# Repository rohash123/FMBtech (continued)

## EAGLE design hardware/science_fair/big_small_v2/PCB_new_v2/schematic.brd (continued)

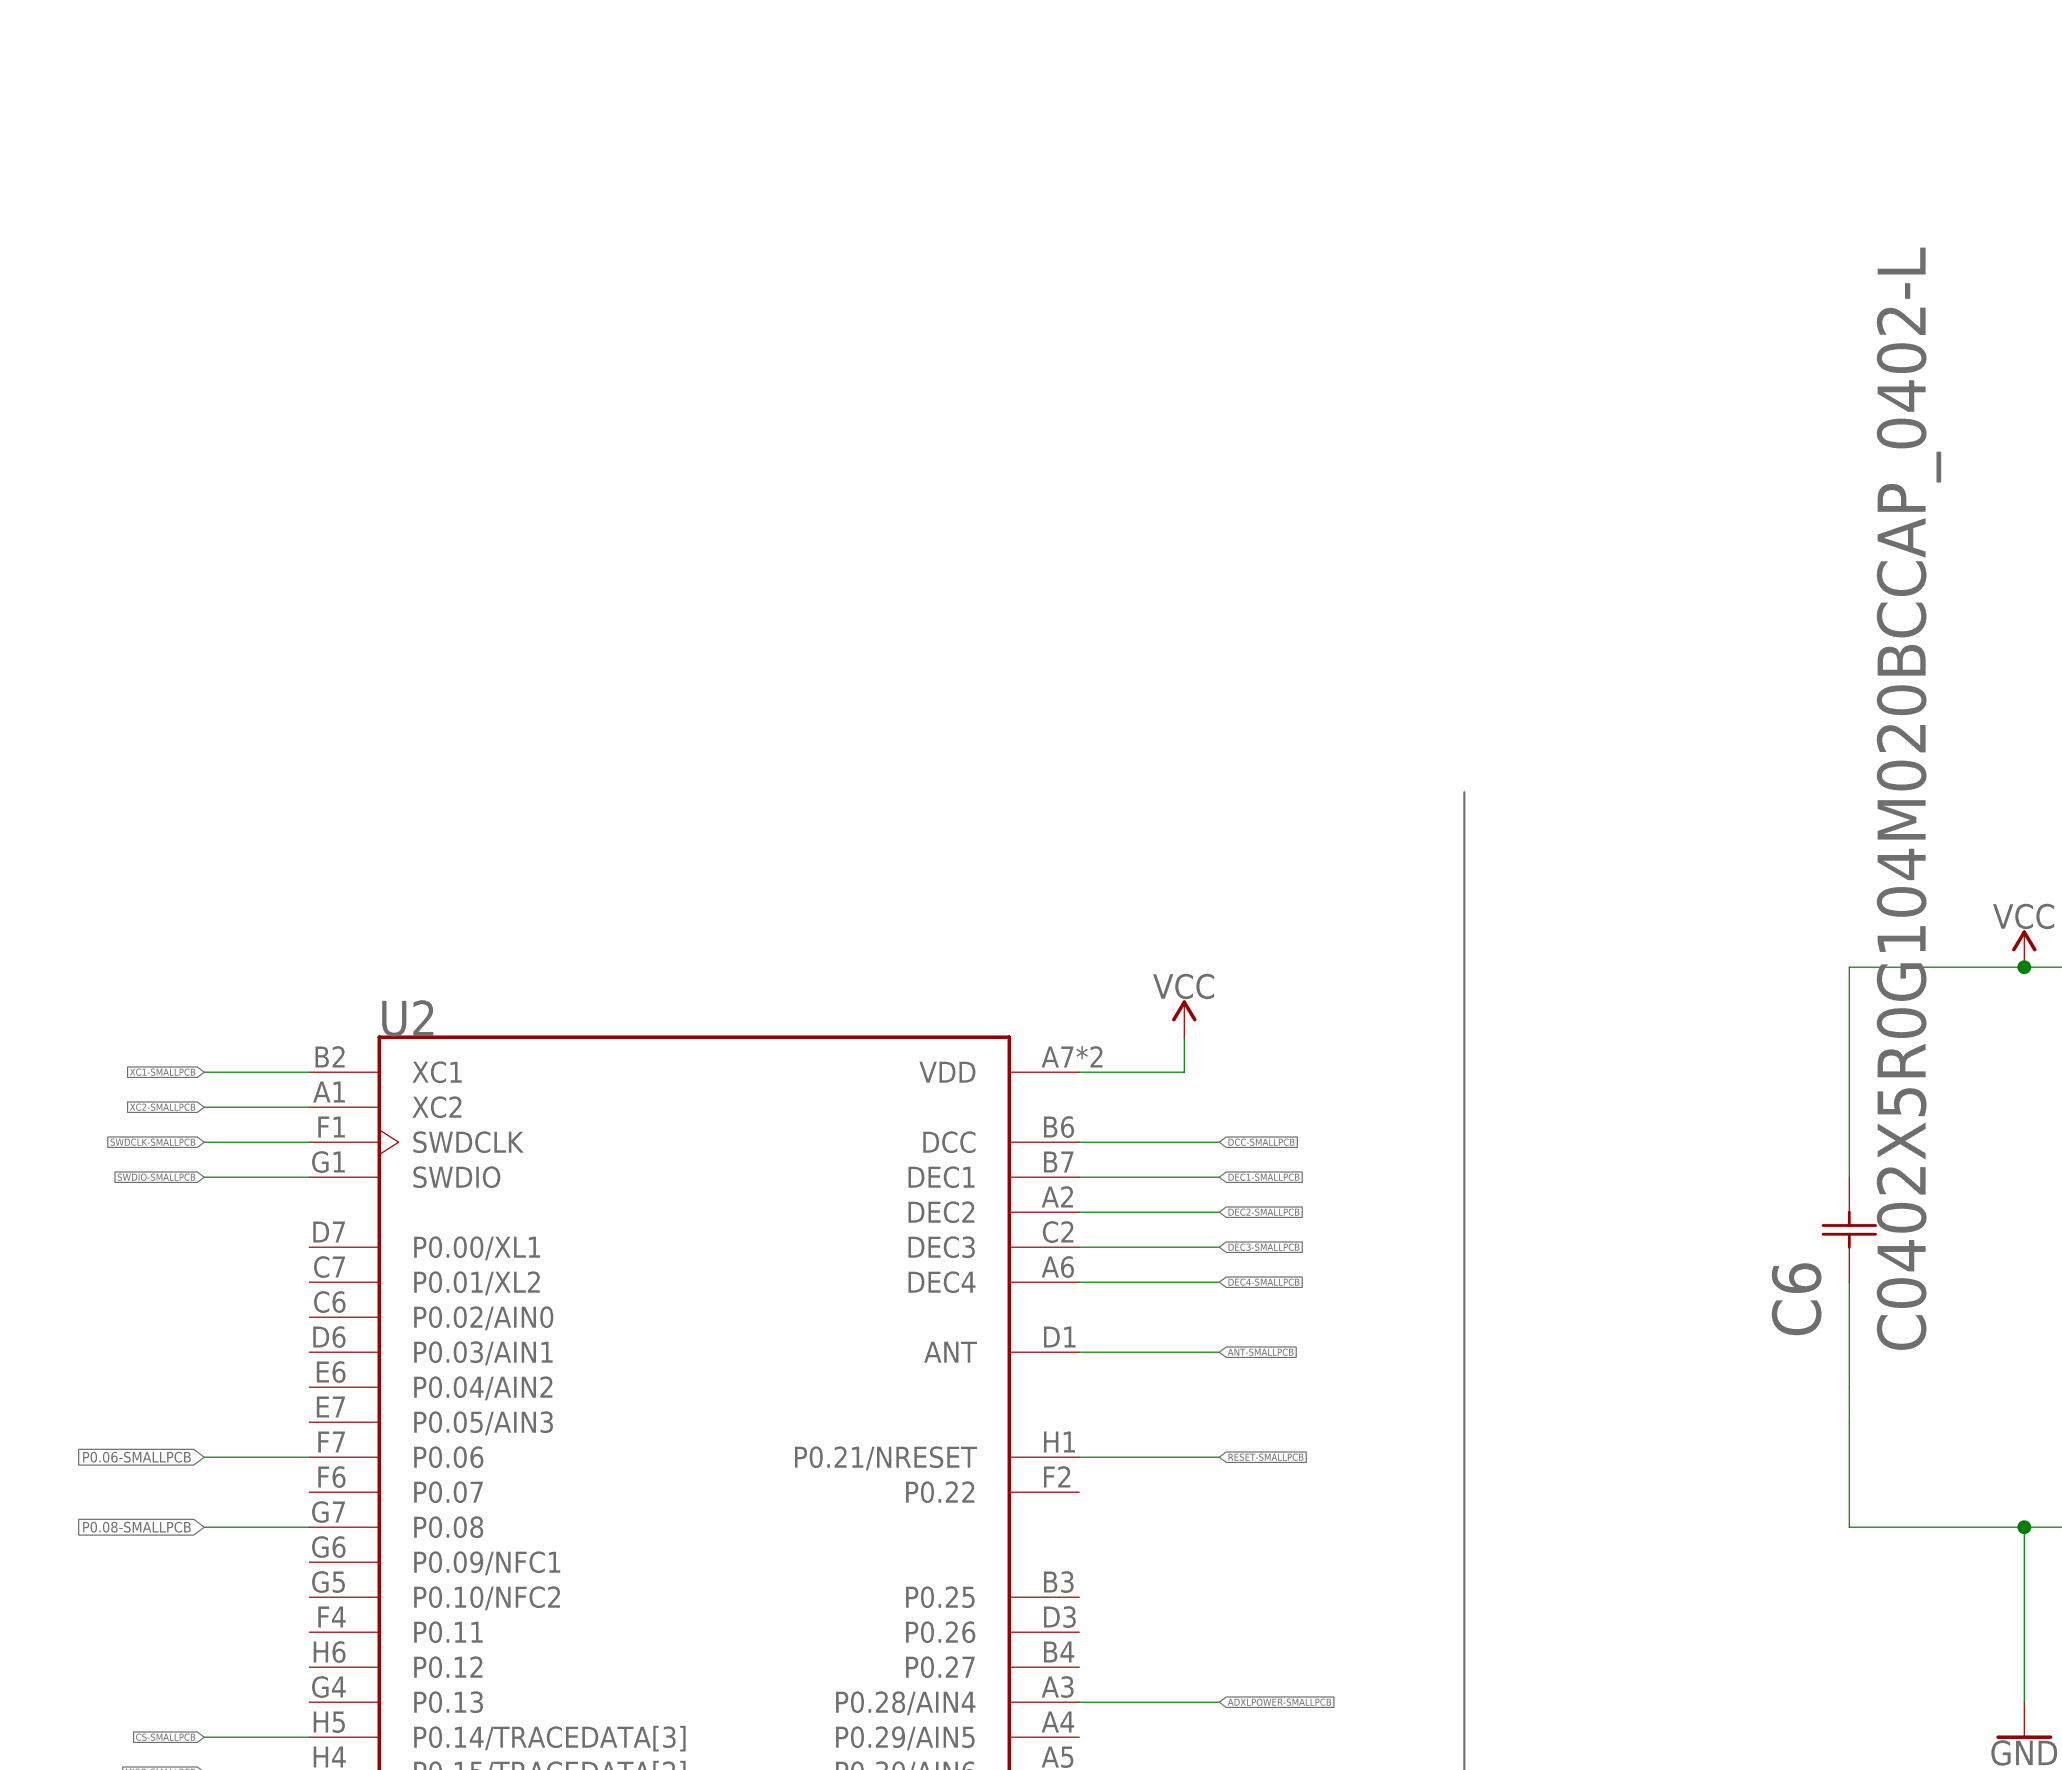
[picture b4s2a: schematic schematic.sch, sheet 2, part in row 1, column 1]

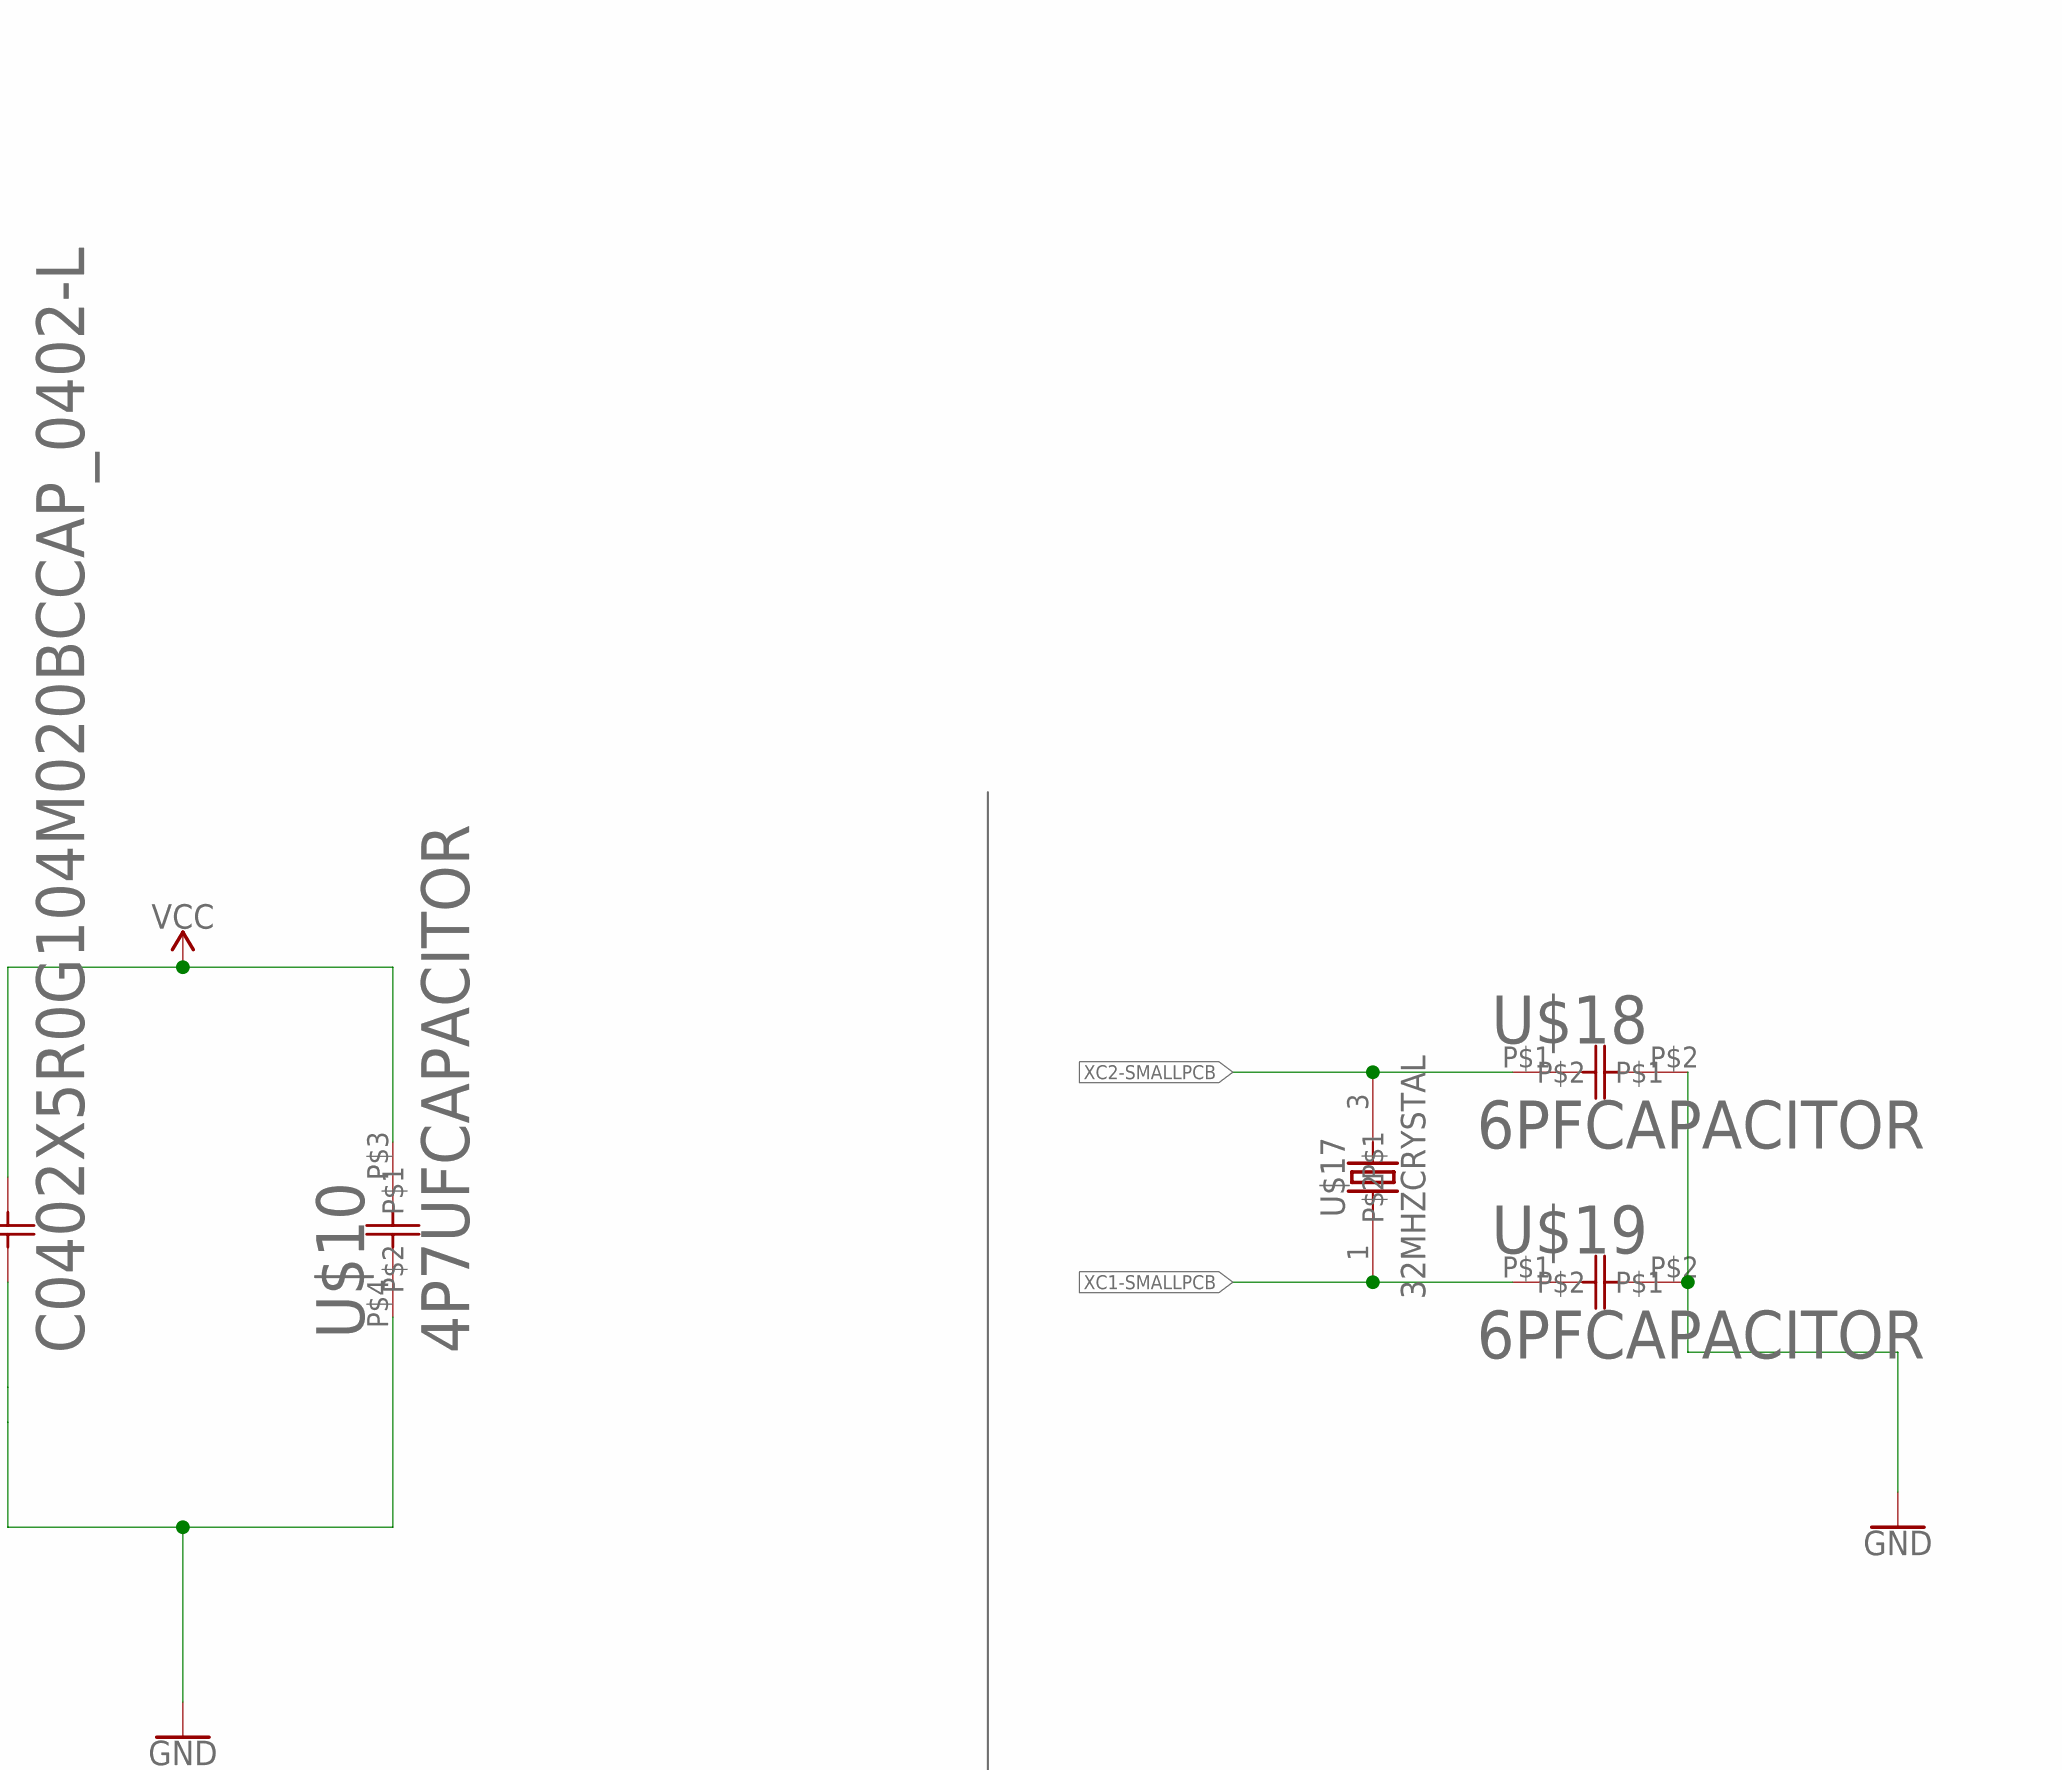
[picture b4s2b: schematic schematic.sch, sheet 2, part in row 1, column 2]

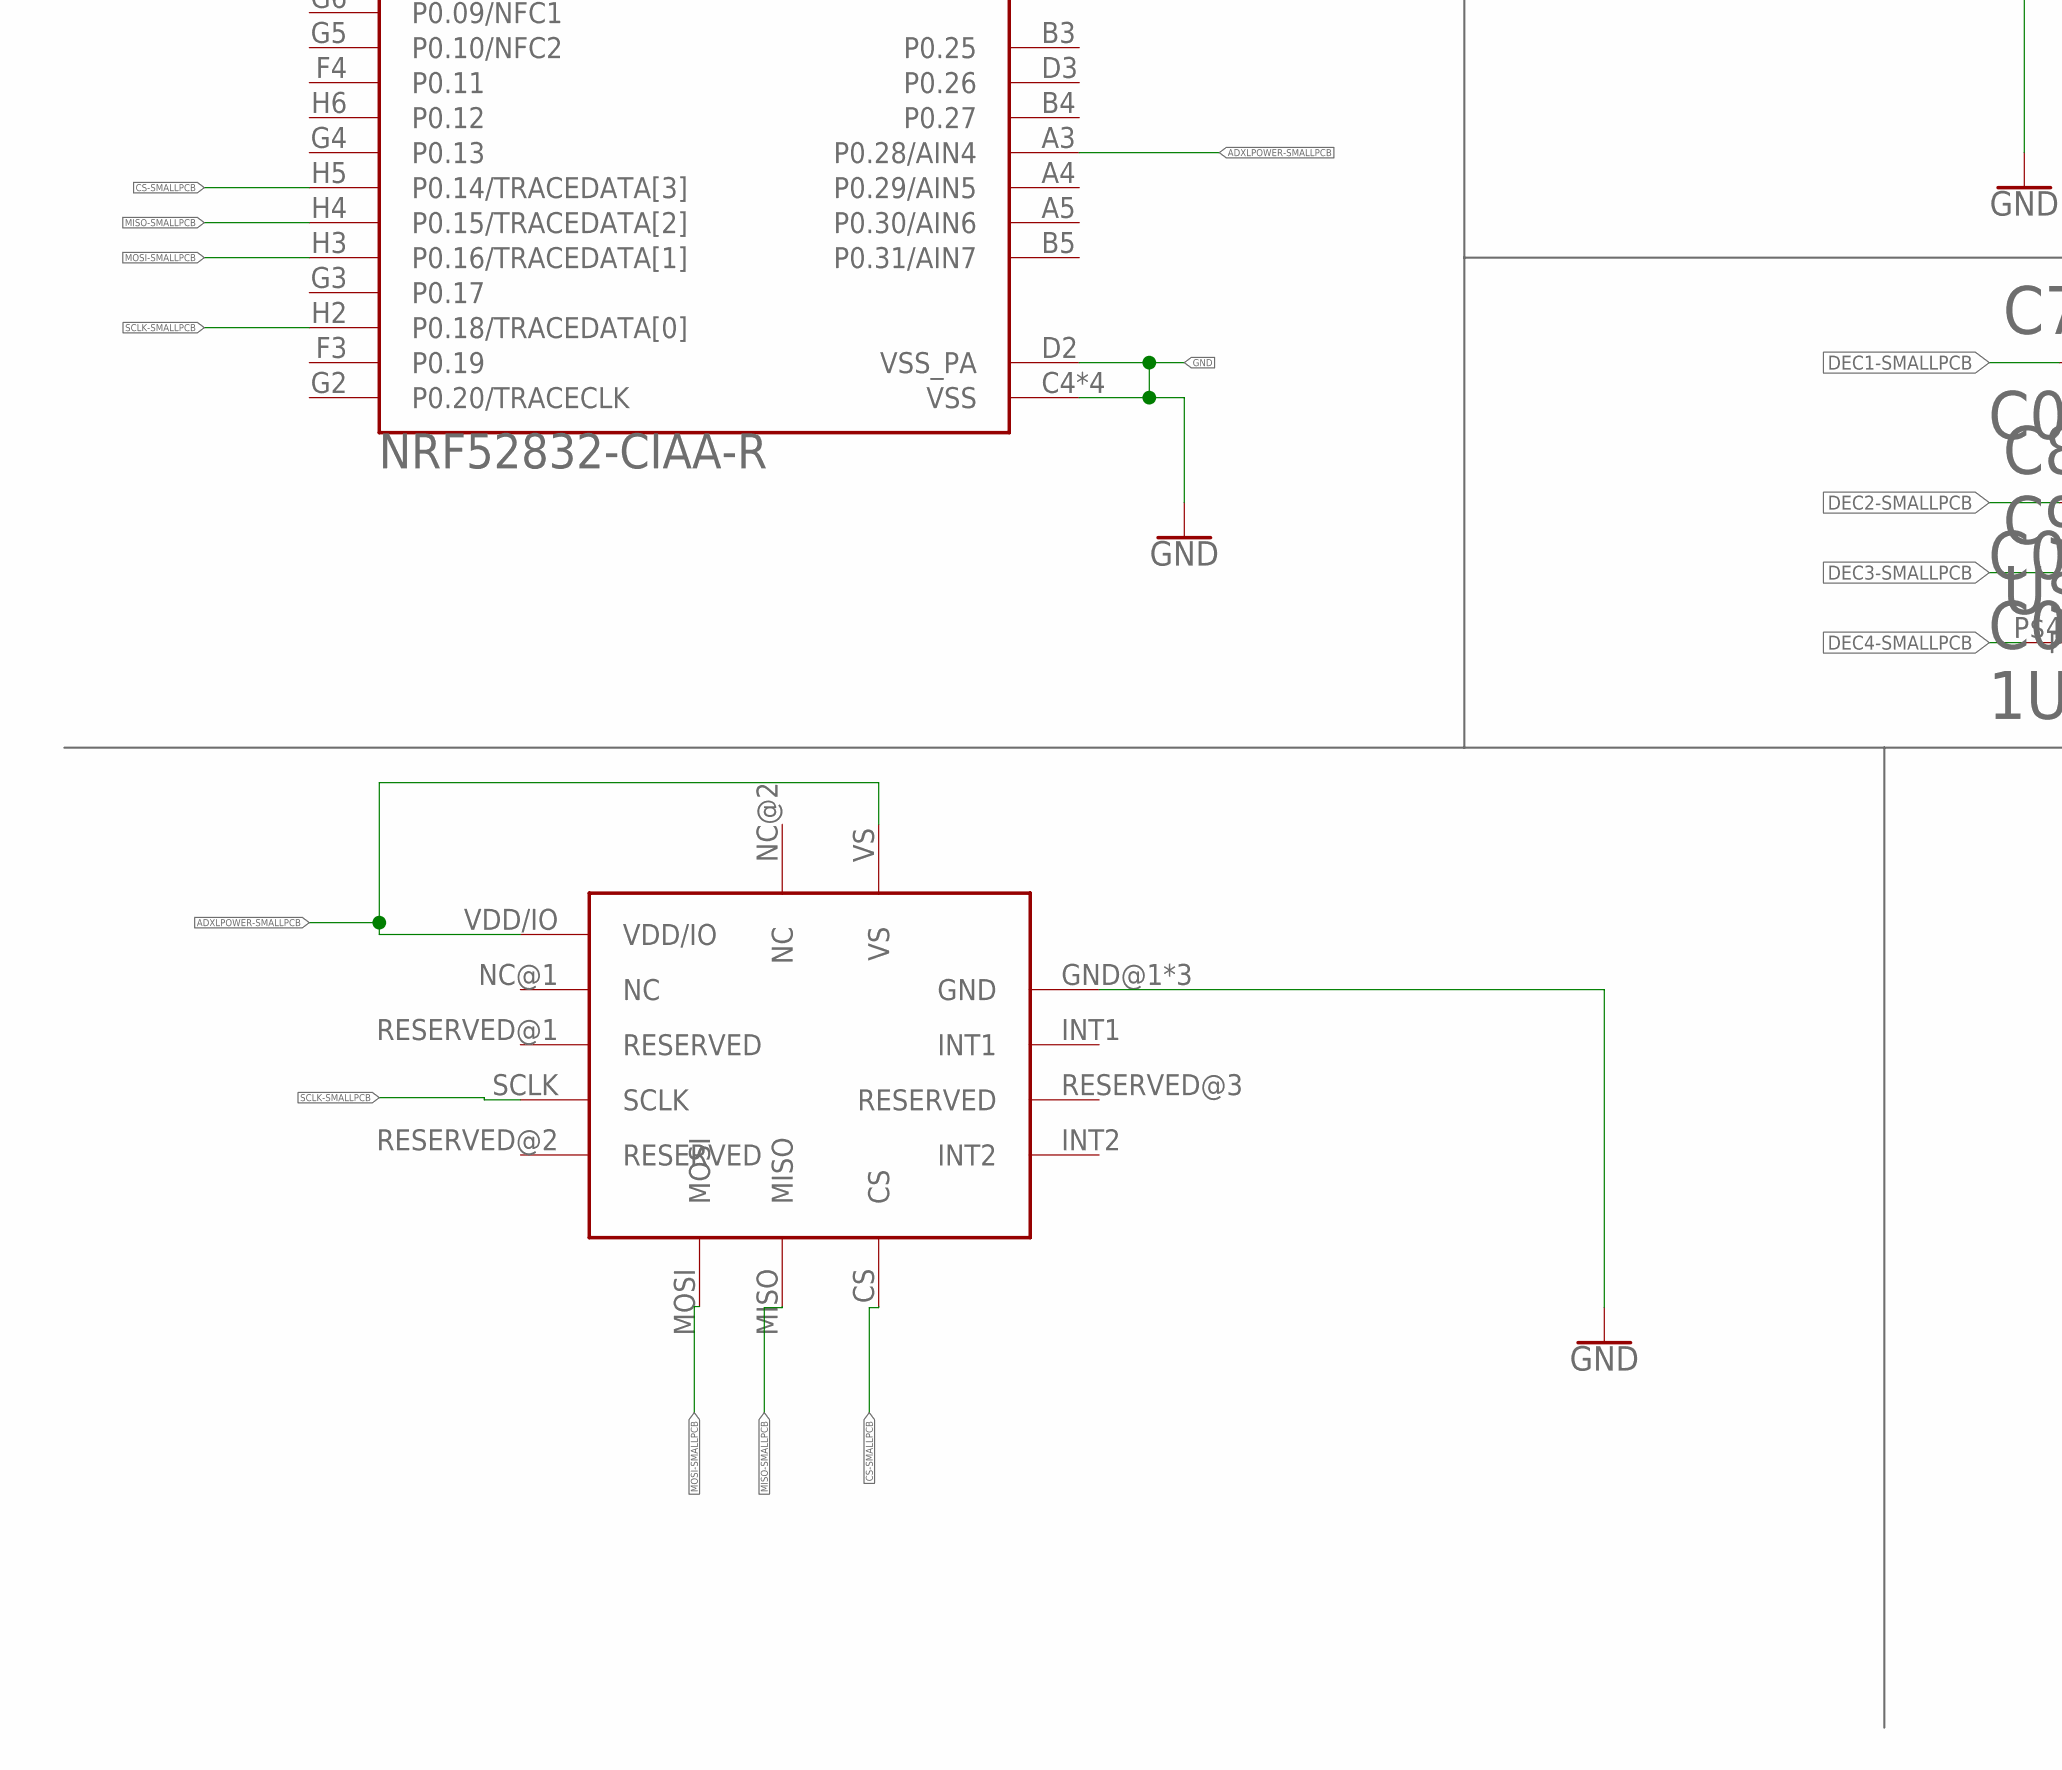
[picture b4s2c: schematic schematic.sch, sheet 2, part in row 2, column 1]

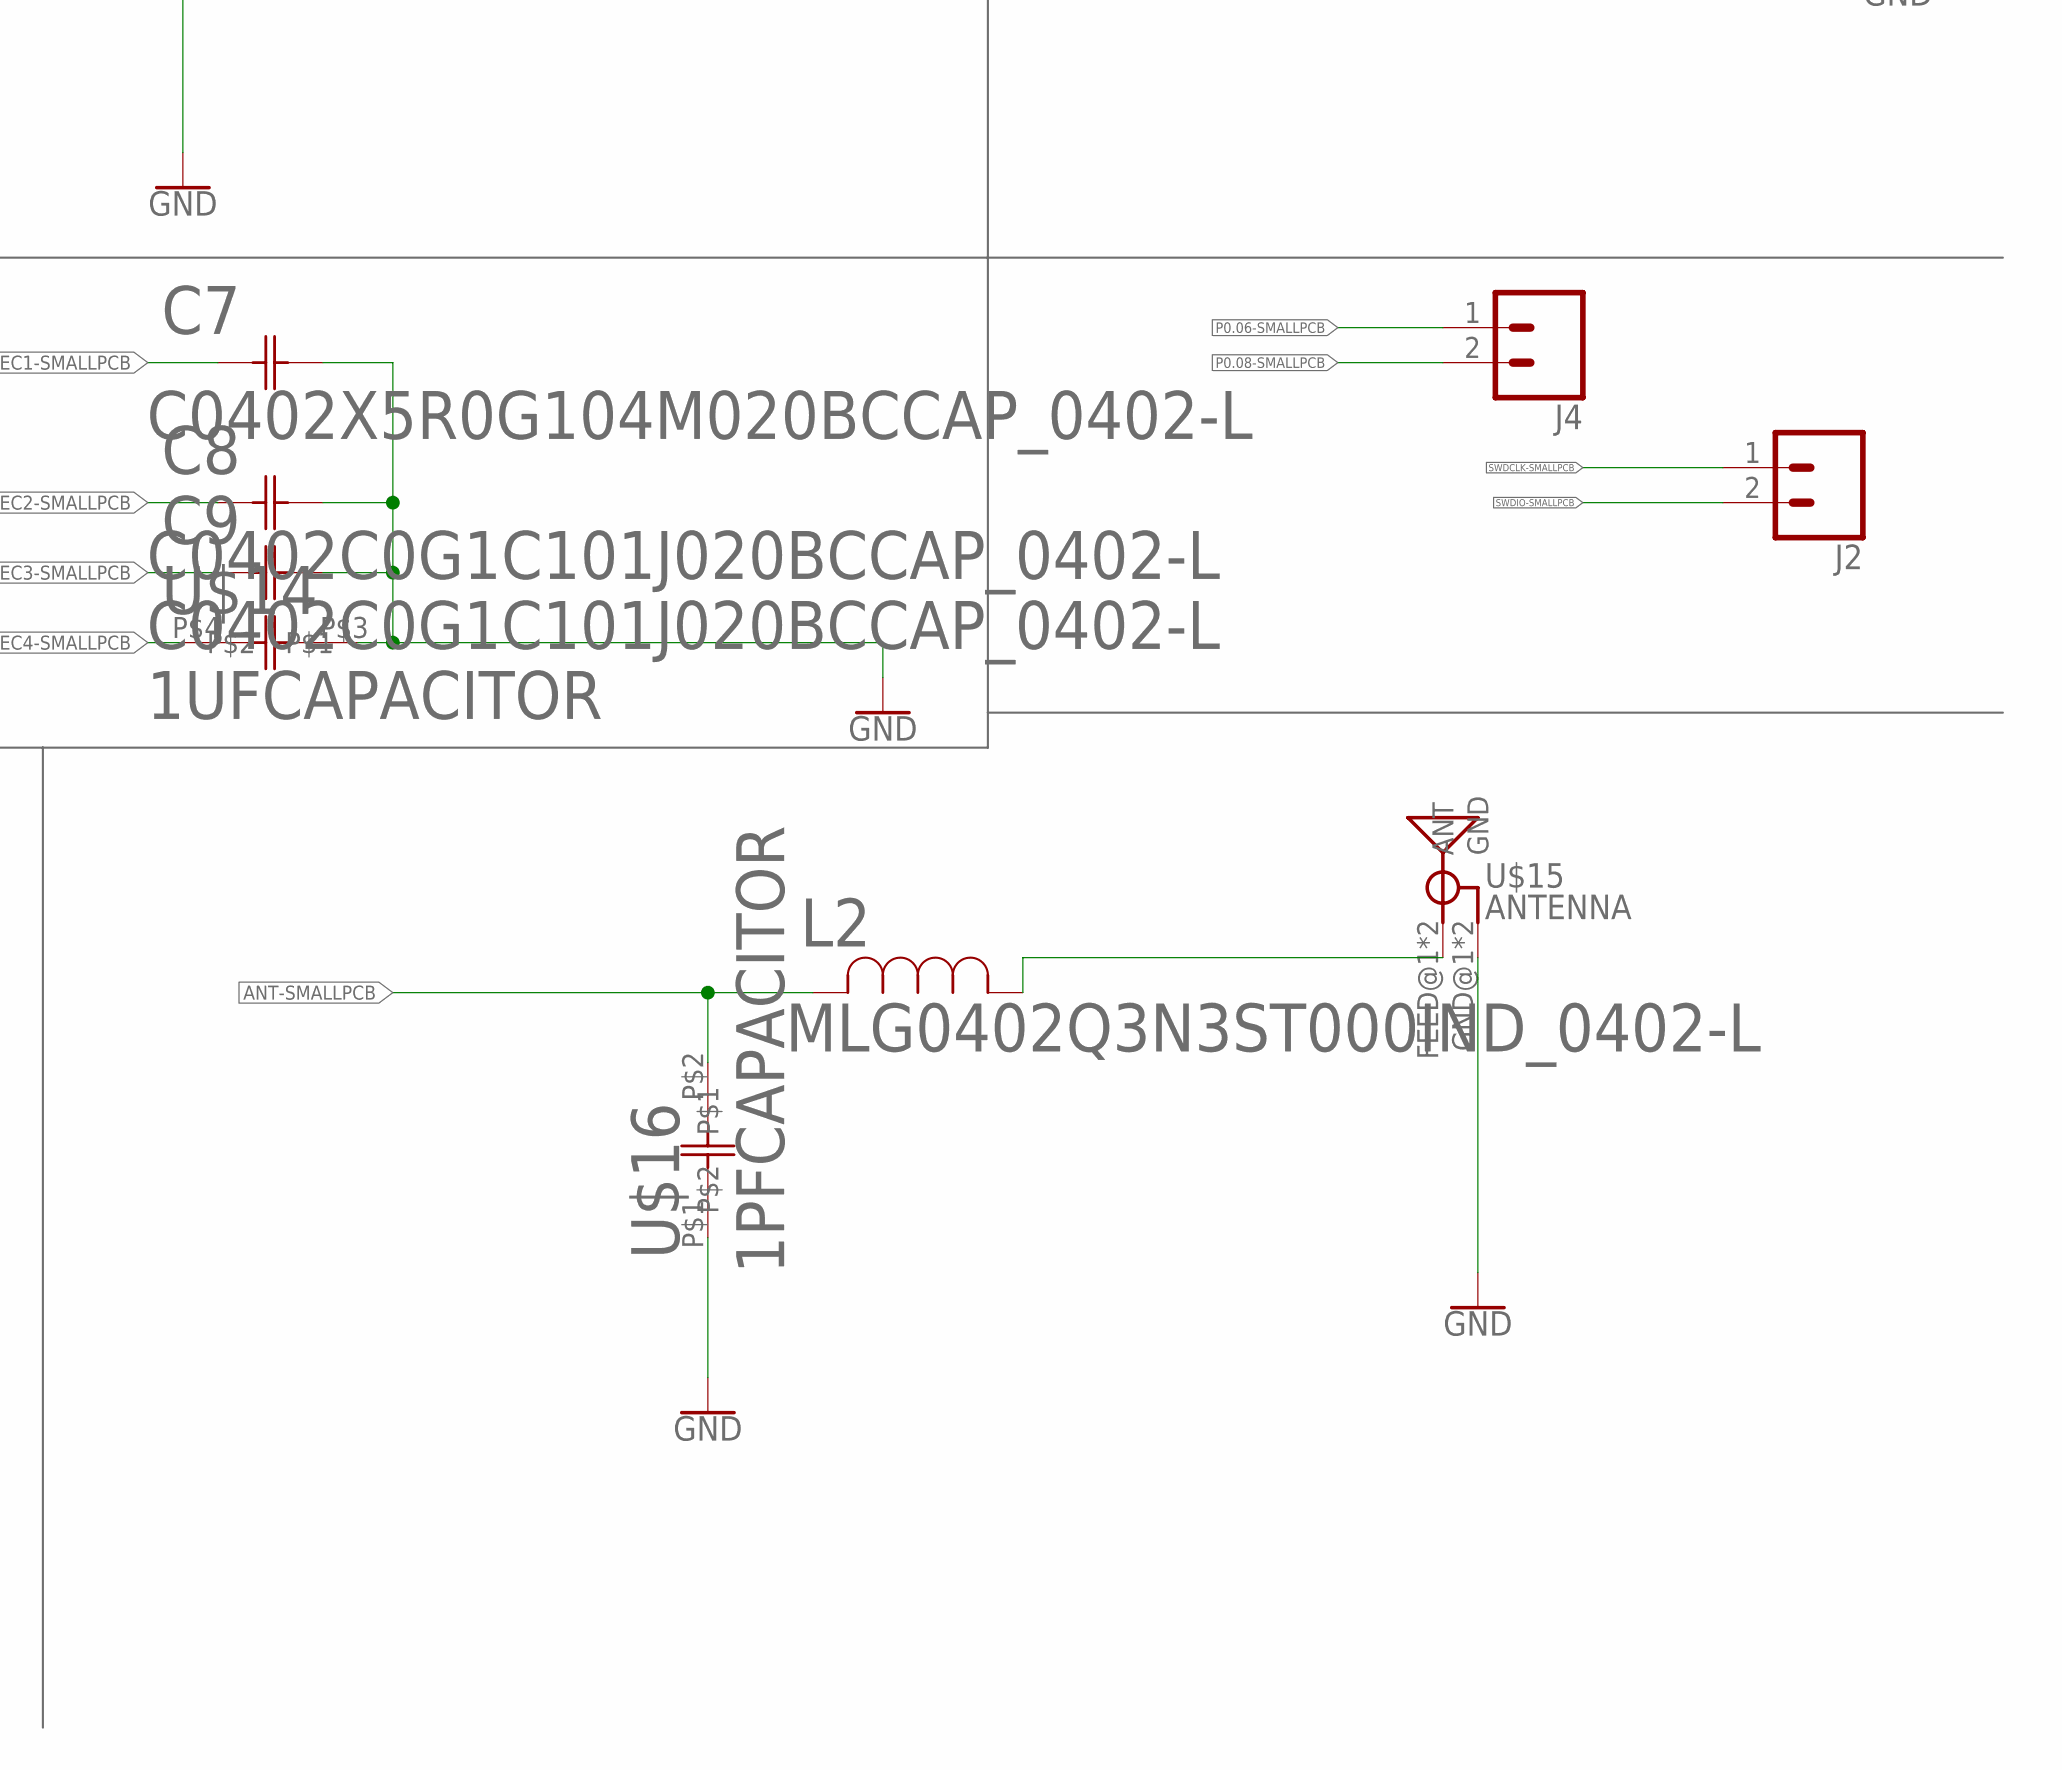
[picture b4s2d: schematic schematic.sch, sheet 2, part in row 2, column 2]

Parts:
C6, C7: C0402X5R0G104M020BCCAP_0402-L; CAP_0402-L
C8, C9: C0402C0G1C101J020BCCAP_0402-L; CAP_0402-L
J2, J4: CONN_02; 1X02
L2: MLG0402Q3N3ST000IND_0402-L; IND_0402-L
U2: NRF52832-CIAA-R; BGA50N40P7X8_300X320X40
U$8: ADXL362; TFLGA-16/3.3MMX3.1MM
U$10: 4P7UFCAPACITOR
U$14: 1UFCAPACITOR
U$15: ANTENNA; ANTENNA_FOOTPRINT
U$16: 1PFCAPACITOR
U$17: 32MHZCRYSTAL
U$18, U$19: 6PFCAPACITOR

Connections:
ADXLPOWER-SMALLPCB: U2.A3 (P0.28/AIN4), U$8.VDD/IO, U$8.VS
ANT-SMALLPCB: L2.2, U2.D1 (ANT), U$16.P$2
CS-SMALLPCB: U2.H5 (P0.14/TRACEDATA[3]), U$8.CS
DCC-SMALLPCB: U2.B6 (DCC)
DEC1-SMALLPCB: C7.1 (11), U2.B7 (DEC1)
DEC2-SMALLPCB: C8.1 (11), U2.A2 (DEC2)
DEC3-SMALLPCB: C9.1 (11), U2.C2 (DEC3)
DEC4-SMALLPCB: U2.A6 (DEC4), U$14.P$4
GND: C6.1 (11), C7.2 (22), C8.2 (22), C9.2 (22), U2.C4 (VSS), U2.C5 (VSS), U2.D2 (VSS_PA), U2.E3 (VSS), U2.F5 (VSS), U$8.GND@1 (GND), U$8.GND@2 (GND), U$8.GND@3 (GND), U$10.P$4, U$14.P$3, U$15.GND@1 (GND), U$15.GND@2 (GND), U$16.P$1, U$18.P$2, U$19.P$2
MISO-SMALLPCB: U2.H4 (P0.15/TRACEDATA[2]), U$8.MISO
MOSI-SMALLPCB: U2.H3 (P0.16/TRACEDATA[1]), U$8.MOSI
unnamed: L2.1, U$15.FEED@1 (ANT), U$15.FEED@2 (ANT)
P0.06-SMALLPCB: J4.1, U2.F7 (P0.06)
P0.08-SMALLPCB: J4.2, U2.G7 (P0.08)
RESET-SMALLPCB: U2.H1 (P0.21/NRESET)
SCLK-SMALLPCB: U2.H2 (P0.18/TRACEDATA[0]), U$8.SCLK
SWDCLK-SMALLPCB: J2.1, U2.F1 (SWDCLK)
SWDIO-SMALLPCB: J2.2, U2.G1 (SWDIO)
VCC: C6.2 (22), U2.A7 (VDD), U2.H7 (VDD), U$10.P$3
XC1-SMALLPCB: U2.B2 (XC1), U$17.1, U$19.P$1
XC2-SMALLPCB: U2.A1 (XC2), U$17.3, U$18.P$1

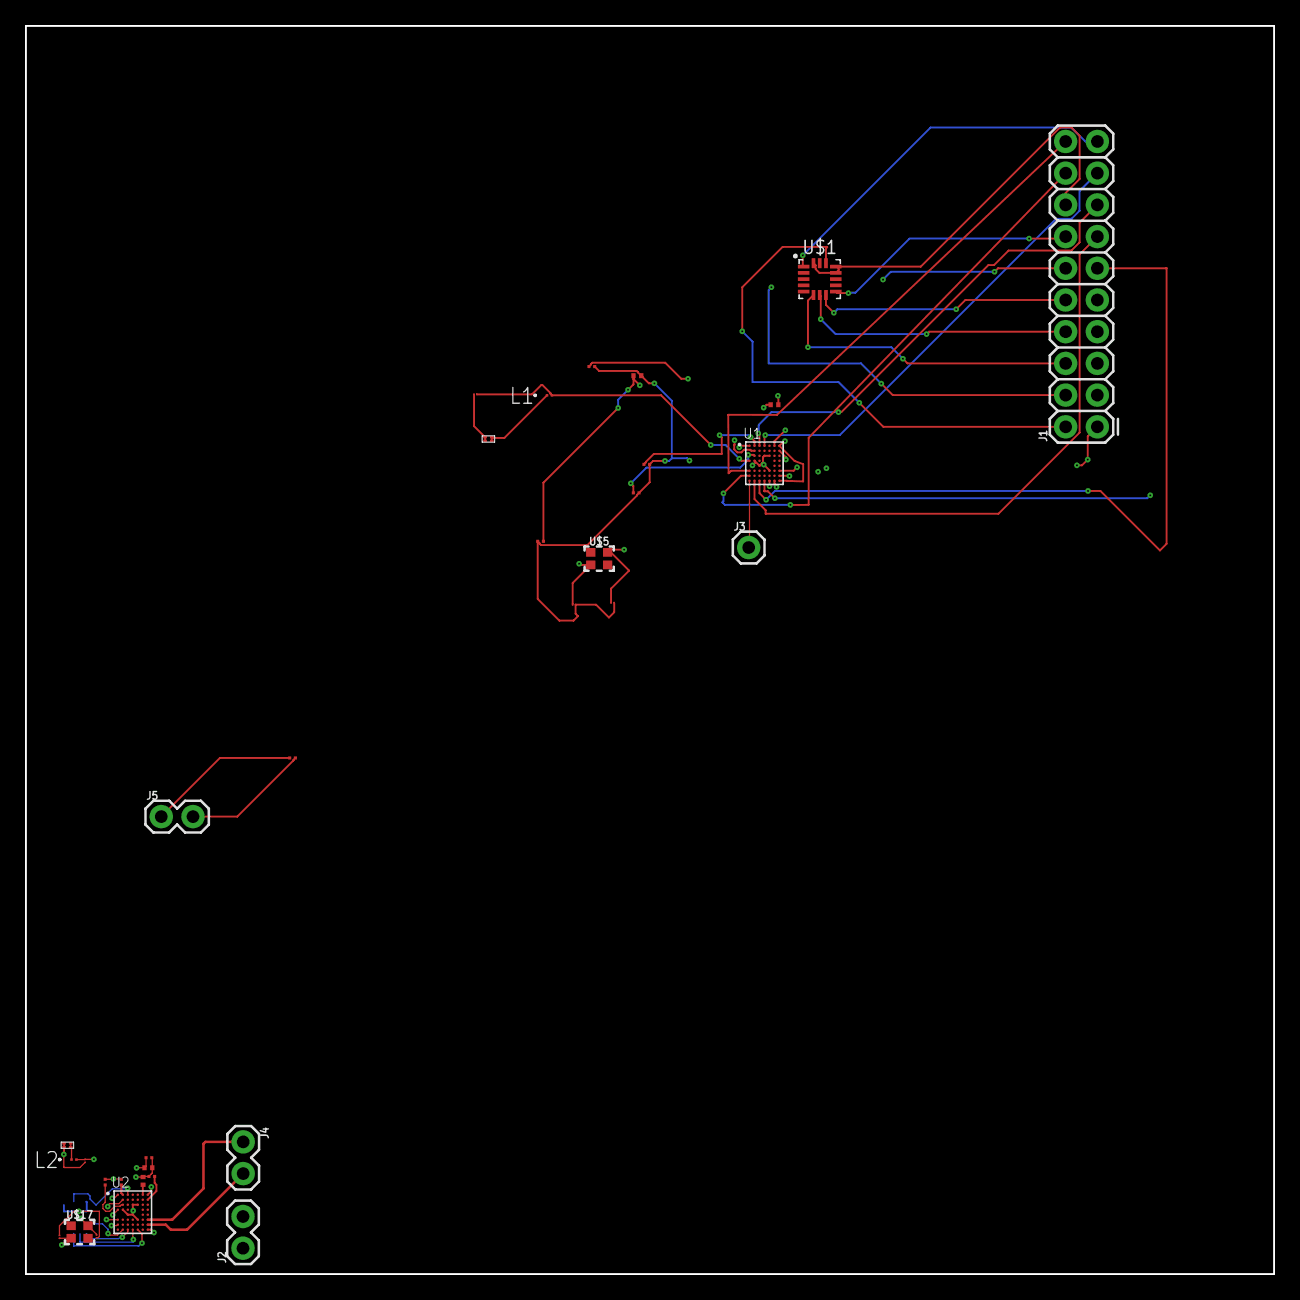
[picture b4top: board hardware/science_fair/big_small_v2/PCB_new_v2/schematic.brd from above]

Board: 6 copper layers, 100.0 x 100.0 mm, 34 parts (1 on the bottom side), 53 nets.

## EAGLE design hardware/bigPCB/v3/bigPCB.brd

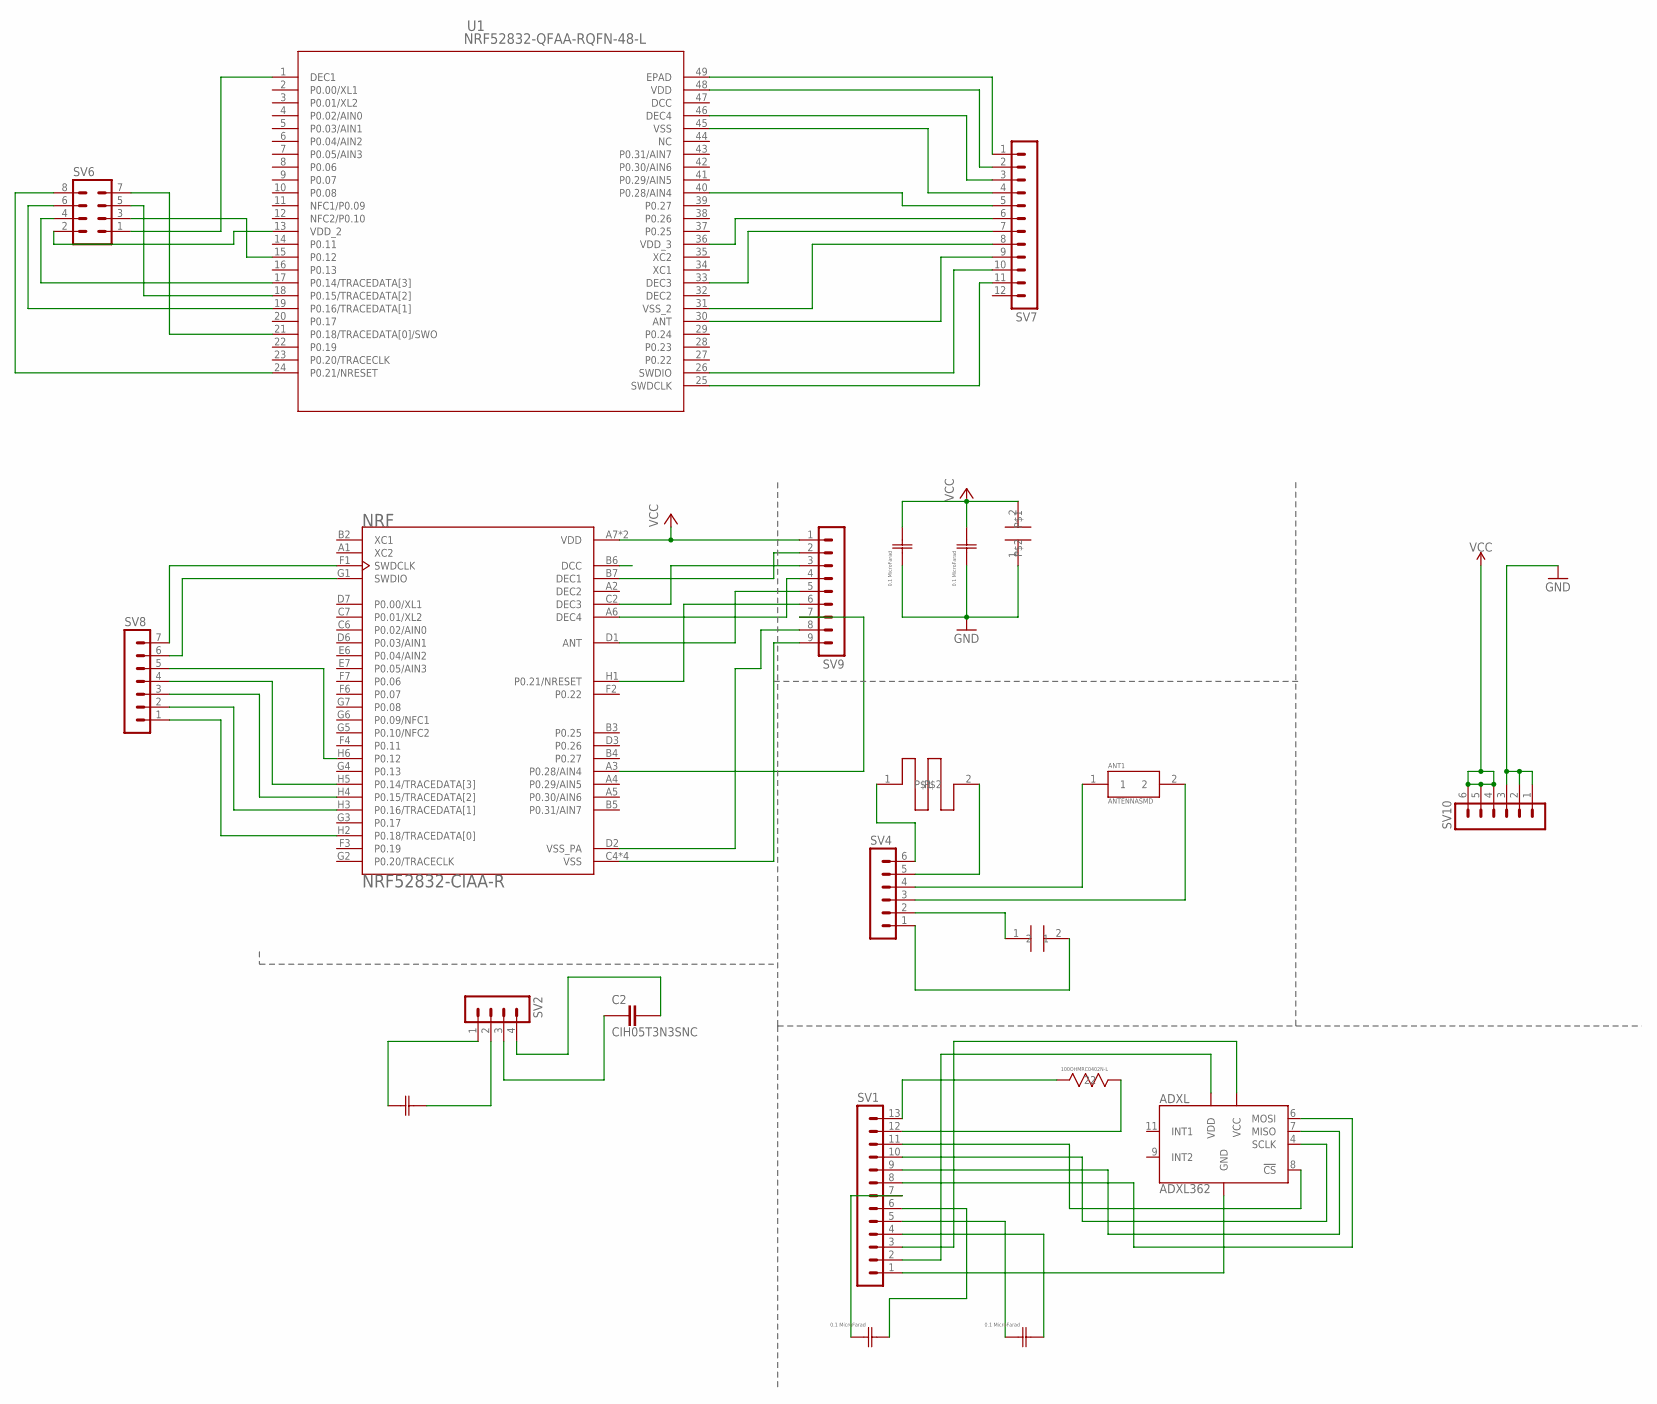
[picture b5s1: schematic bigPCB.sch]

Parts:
ADXL: ADXL362; TFLGA-16/3.3MMX3.1MM
ANT1: ANTENNASMD; 1
C1: GJM1555C1H1R0BB01DG-155-L; G-155-L
C2: CIH05T3N3SNC; CAPC1005X55N
C6, C7, C8, C9: 02016D104KAT2A; 0201
NRF: NRF52832-CIAA-R; BGA50N40P7X8_300X320X40
R6: 100OHMRC0402N-L; RES
SV1: MA13-1
SV2: MA04-1
SV4, SV10: MA06-1
SV6: MA04-2
SV7: MA12-1
SV8: MA07-1
SV9: MA09-1
U1: NRF52832-QFAA-RQFN-48-L; QFN-48-L
U$1: 4.7µF; CAP
U$2: 0.8PF; CAP
U$3: INDUCTOR; 1

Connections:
DCC: U1.47 (DCC)
DEC2: NRF.A2 (DEC2), U1.32 (DEC2)
GND: C6.1, C7.1, SV10.1, SV10.2, SV10.3, U$1.1
unnamed: SV6.1, U1.1 (DEC1)
unnamed: NRF.B7 (DEC1), SV9.2
unnamed: R6.1 (11), SV1.13
unnamed: R6.2 (22), SV1.12
unnamed: SV4.6, U$3.1
unnamed: NRF.C2 (DEC3), SV9.3
unnamed: SV6.3, U1.15 (P0.12)
unnamed: NRF.A6 (DEC4), SV9.4
unnamed: NRF.D1 (ANT), SV9.5
unnamed: ADXL.12 (GND), ADXL.13 (GND), ADXL.16 (GND), SV1.1
unnamed: SV6.4, U1.17 (P0.14/TRACEDATA[3])
unnamed: SV6.5, U1.18 (P0.15/TRACEDATA[2])
unnamed: SV6.6, U1.19 (P0.16/TRACEDATA[1])
unnamed: SV6.7, U1.21 (P0.18/TRACEDATA[0]/SWO)
unnamed: SV6.8, U1.24 (P0.21/NRESET)
unnamed: SV7.3, U1.46 (DEC4)
unnamed: SV7.7, U1.33 (DEC3)
unnamed: NRF.F1 (SWDCLK), SV8.7
unnamed: NRF.G1 (SWDIO), SV8.6
unnamed: NRF.H6 (P0.12), SV8.5
unnamed: NRF.H5 (P0.14/TRACEDATA[3]), SV8.4
unnamed: NRF.H4 (P0.15/TRACEDATA[2]), SV8.3
unnamed: NRF.H3 (P0.16/TRACEDATA[1]), SV8.2
unnamed: NRF.H2 (P0.18/TRACEDATA[0]), SV8.1
unnamed: SV7.1, U1.49 (EPAD)
unnamed: NRF.H1 (P0.21/NRESET), SV9.6
unnamed: SV7.4, U1.45 (VSS)
unnamed: SV7.5, U1.40 (P0.28/AIN4)
unnamed: NRF.A3 (P0.28/AIN4), SV9.7
unnamed: SV7.11, U1.25 (SWDCLK)
unnamed: SV7.10, U1.26 (SWDIO)
unnamed: SV7.9, U1.30 (ANT)
unnamed: SV7.8, U1.31 (VSS_2)
unnamed: NRF.D2 (VSS_PA), SV9.8
unnamed: NRF.C4 (VSS), NRF.C5 (VSS), NRF.E3 (VSS), NRF.F5 (VSS), SV9.9
unnamed: SV4.5, U$3.2
unnamed: ANT1.1, SV4.4
unnamed: ANT1.2, SV4.3
unnamed: SV4.1, U$2.2
unnamed: SV4.2, U$2.1
unnamed: ADXL.1 (VDD), SV1.2
unnamed: ADXL.14 (VCC), SV1.3
unnamed: ADXL.8 (!CS), SV1.11
unnamed: ADXL.4 (SCLK), SV1.10
unnamed: ADXL.7 (MISO), SV1.9
unnamed: ADXL.6 (MOSI), SV1.8
unnamed: C8.1, SV1.7
unnamed: C8.2, SV1.6
unnamed: C9.1, SV1.5
unnamed: C9.2, SV1.4
unnamed: C1.1 (11), SV2.1
unnamed: C1.2 (22), SV2.2
unnamed: C2.1, SV2.3
unnamed: C2.2, SV2.4
VCC: C6.2, C7.2, NRF.A7 (VDD), NRF.H7 (VDD), SV6.2, SV7.2, SV7.6, SV9.1, SV10.4, SV10.5, SV10.6, U1.13 (VDD_2), U1.36 (VDD_3), U1.48 (VDD), U$1.2

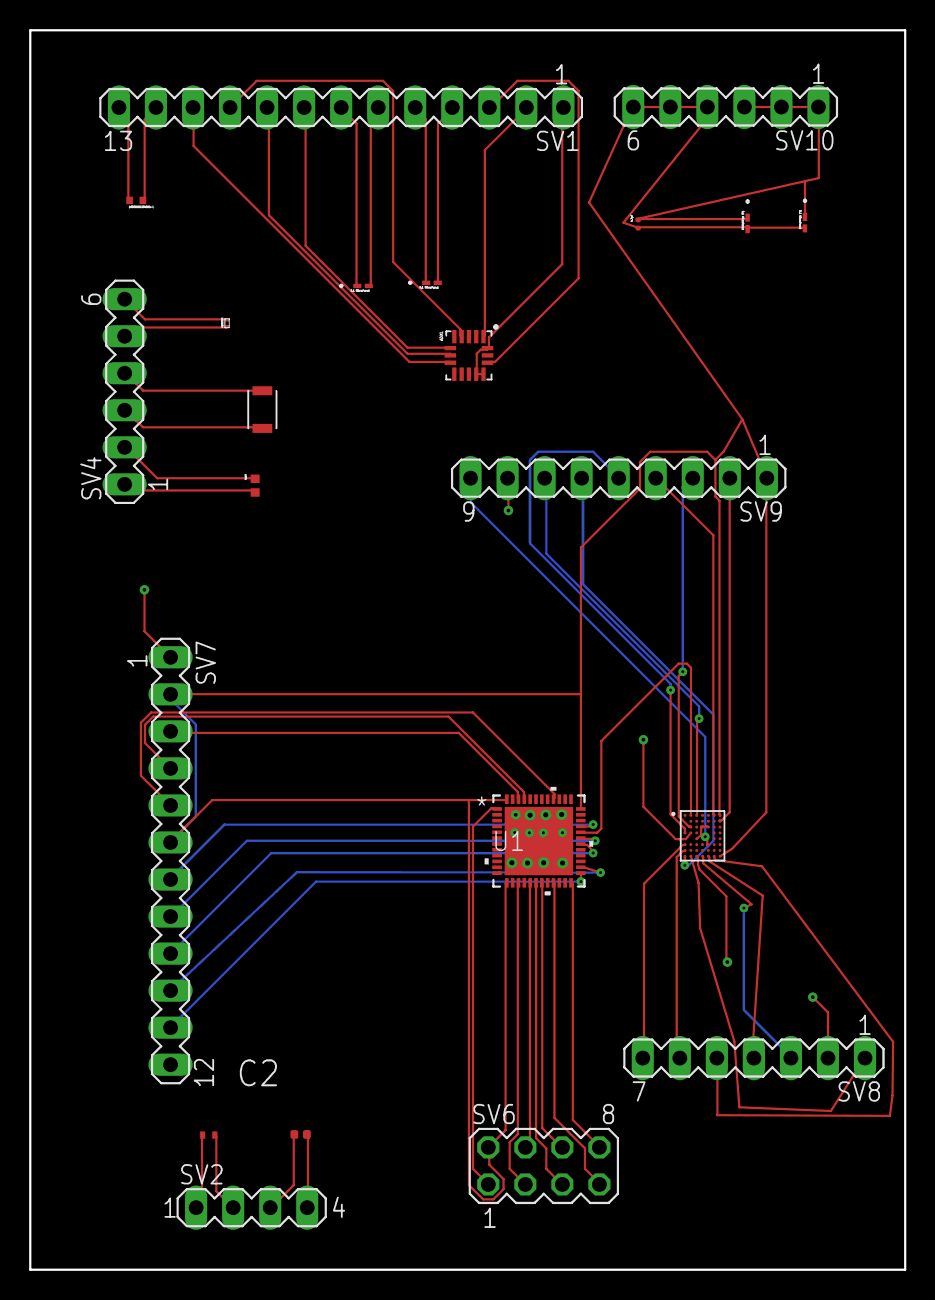
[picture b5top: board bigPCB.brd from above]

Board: 4 copper layers, 60.0 x 85.0 mm, 22 parts (0 on the bottom side), 57 nets.
